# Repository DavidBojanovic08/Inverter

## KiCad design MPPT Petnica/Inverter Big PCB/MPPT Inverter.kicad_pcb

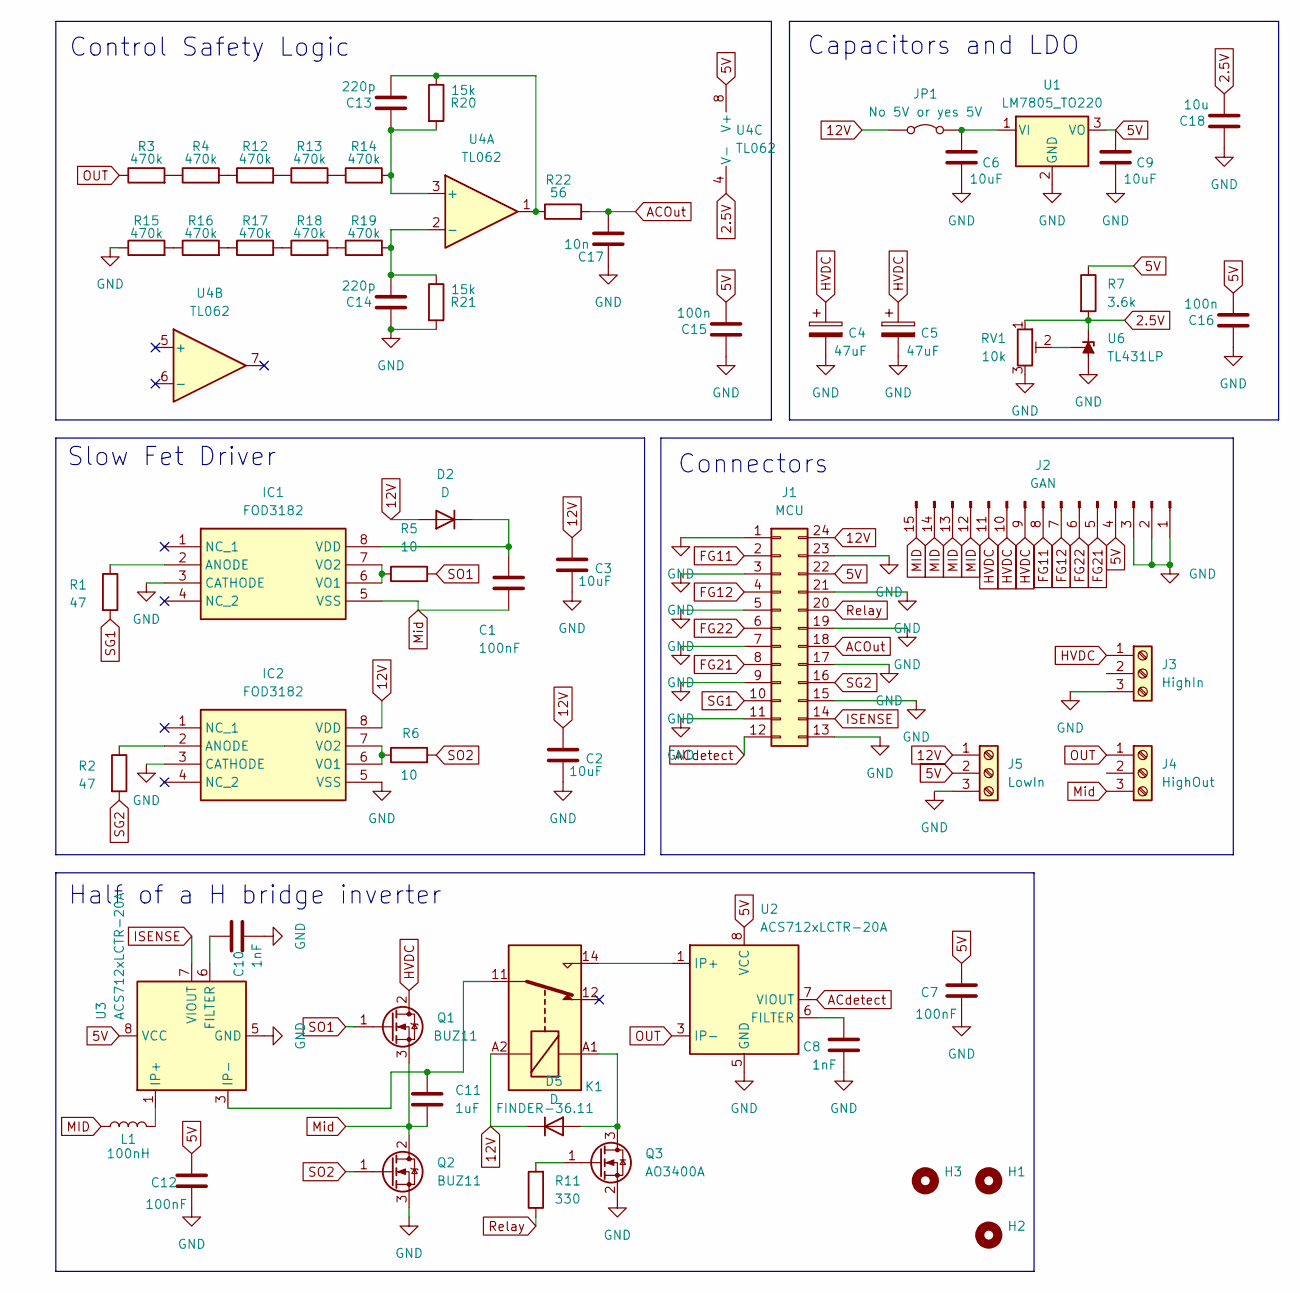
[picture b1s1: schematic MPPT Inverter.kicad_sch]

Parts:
C1, C7, C12: 100nF; C_0603_1608Metric
C2, C3, C6, C9: 10uF; C_0805_2012Metric
C4, C5: 47uF; CP_Radial_D16.0mm_P7.50mm
C8, C10: 1nF; C_0805_2012Metric
C11: 1uF; C_Rect_L29.0mm_W11.0mm_P27.50mm_MKT
C13, C14: 220p; C_0603_1608Metric
C15, C16: 100n; C_0603_1608Metric
C17: 10n; C_0603_1608Metric
C18: 10u; C_0805_2012Metric
D2: D; D_0603_1608Metric
D5: D; D_0805_2012Metric
H1, H2, H3: MountingHole; MountingHole_3.2mm_M3
IC1, IC2: FOD3182; Manufacturer_Part_Number FOD3182; Mouser Part Number 512-FOD3182
J1: MCU; IDC-Header_2x12_P2.54mm_Vertical
J2: GAN; PinHeader_1x15_P2.54mm_Vertical
J3: HighIn; TerminalBlock_MaiXu_MX126-5.0-03P_1x03_P5.00mm
J4: HighOut; TerminalBlock_MaiXu_MX126-5.0-03P_1x03_P5.00mm
J5: LowIn; TerminalBlock_MaiXu_MX126-5.0-03P_1x03_P5.00mm
JP1: No 5V or yes 5V; R_0402_1005Metric
K1: FINDER-36.11; Relay_SPDT_Finder_36.11
L1: 100nH; L_Toroid_Vertical_L31.8mm_W15.9mm_P13.50mm_Bourns_5700
Q1, Q2: BUZ11; TO-220-3_Vertical
Q3: AO3400A; SOT-23
R1, R2: 47; R_0603_1608Metric
R3, R4, R12, R13, R14, R15, R16, R17, R18, R19: 470k; R_0603_1608Metric
R5, R6: 10; R_0603_1608Metric
R7: 3.6k; R_0603_1608Metric
R11: 330; R_0603_1608Metric
R20, R21: 15k; R_0603_1608Metric
R22: 56; R_0603_1608Metric
RV1: 10k; Potentiometer_Bourns_3266W_Vertical
U1: LM7805_TO220; TO-220-3_Vertical
U2, U3: ACS712xLCTR-20A; SOIC-8_3.9x4.9mm_P1.27mm
U4: TL062; DIP-8_W7.62mm
U6: TL431LP; TO-92_Inline

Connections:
2.5V: C18.2, R7.2, RV1.1, U4.4 (V-), U6.3 (K)
5V: C7.1, C9.1, C12.1, C15.2, C16.2, J1.22, J2.4, J5.2, R7.1, U1.3 (VO), U2.8 (VCC), U3.8 (VCC), U4.8 (V+)
12V: C2.1, C3.1, D2.2 (A), D5.1 (K), IC2.8 (VDD), J1.24, J5.1, JP1.1 (A), K1.A2
ACOut: C17.2, J1.18, R22.2
ACdetect: J1.12, U2.7 (VIOUT)
FG11: J1.2, J2.8
FG12: J1.4, J2.7
FG21: J1.8, J2.5
FG22: J1.6, J2.6
GND: C2.2, C3.2, C4.2, C5.2, C6.2, C7.2, C8.2, C9.2, C10.2, C12.2, C14.1, C15.1, C16.1, C17.1, C18.1, IC1.3 (CATHODE), IC2.3 (CATHODE), IC2.5 (VSS), J1.1, J1.3, J1.5, J1.7, J1.9, J1.11, J1.13, J1.15, J1.17, J1.19, J1.21, J1.23, J2.1, J2.2, J2.3, J3.3, J5.3, Q2.3 (S), Q3.2 (S), R15.1, R21.2, RV1.3, U1.2 (GND), U2.5 (GND), U3.5 (GND), U6.2 (A)
HVDC: C4.1, C5.1, J2.9, J2.10, J2.11, J3.1, Q1.2 (D)
ISENSE: J1.14, U3.7 (VIOUT)
MID: J2.12, J2.13, J2.14, J2.15, L1.1
Mid: C1.2, C11.1, IC1.5 (VSS), J4.3, Q1.3 (S), Q2.2 (D)
unnamed: C11.2, K1.11, U3.3 (IP-), U3.4 (IP-)
unnamed: C13.2, R20.1, R22.1, U4.1
unnamed: C1.1, D2.1 (K), IC1.8 (VDD)
unnamed: D5.2 (A), K1.A1, Q3.3 (D)
unnamed: IC1.2 (ANODE), R1.1
unnamed: IC1.6 (VO1), IC1.7 (VO2), R5.1
unnamed: IC2.2 (ANODE), R2.1
unnamed: IC2.6 (VO1), IC2.7 (VO2), R6.1
unnamed: C6.1, JP1.2 (B), U1.1 (VI)
unnamed: K1.14, U2.1 (IP+), U2.2 (IP+)
unnamed: L1.2, U3.1 (IP+), U3.2 (IP+)
unnamed: Q3.1 (G), R11.2
unnamed: R3.2, R4.1
unnamed: R4.2, R12.1
unnamed: R12.2, R13.1
unnamed: R13.2, R14.1
unnamed: R15.2, R16.1
unnamed: R16.2, R17.1
unnamed: R17.2, R18.1
unnamed: R18.2, R19.1
unnamed: C8.1, U2.6 (FILTER)
unnamed: C10.1, U3.6 (FILTER)
unnamed: C13.1, R14.2, R20.2, U4.3 (+)
unnamed: C14.2, R19.2, R21.1, U4.2 (-)
unnamed: RV1.2, U6.1 (REF)
OUT: J4.1, R3.1, U2.3 (IP-), U2.4 (IP-)
Relay: J1.20, R11.1
SG1: J1.10, R1.2
SG2: J1.16, R2.2
SO1: Q1.1 (G), R5.2
SO2: Q2.1 (G), R6.2

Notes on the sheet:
Half of a H bridge inverter
Slow Fet Driver
Capacitors and LDO
Connectors
Control Safety Logic

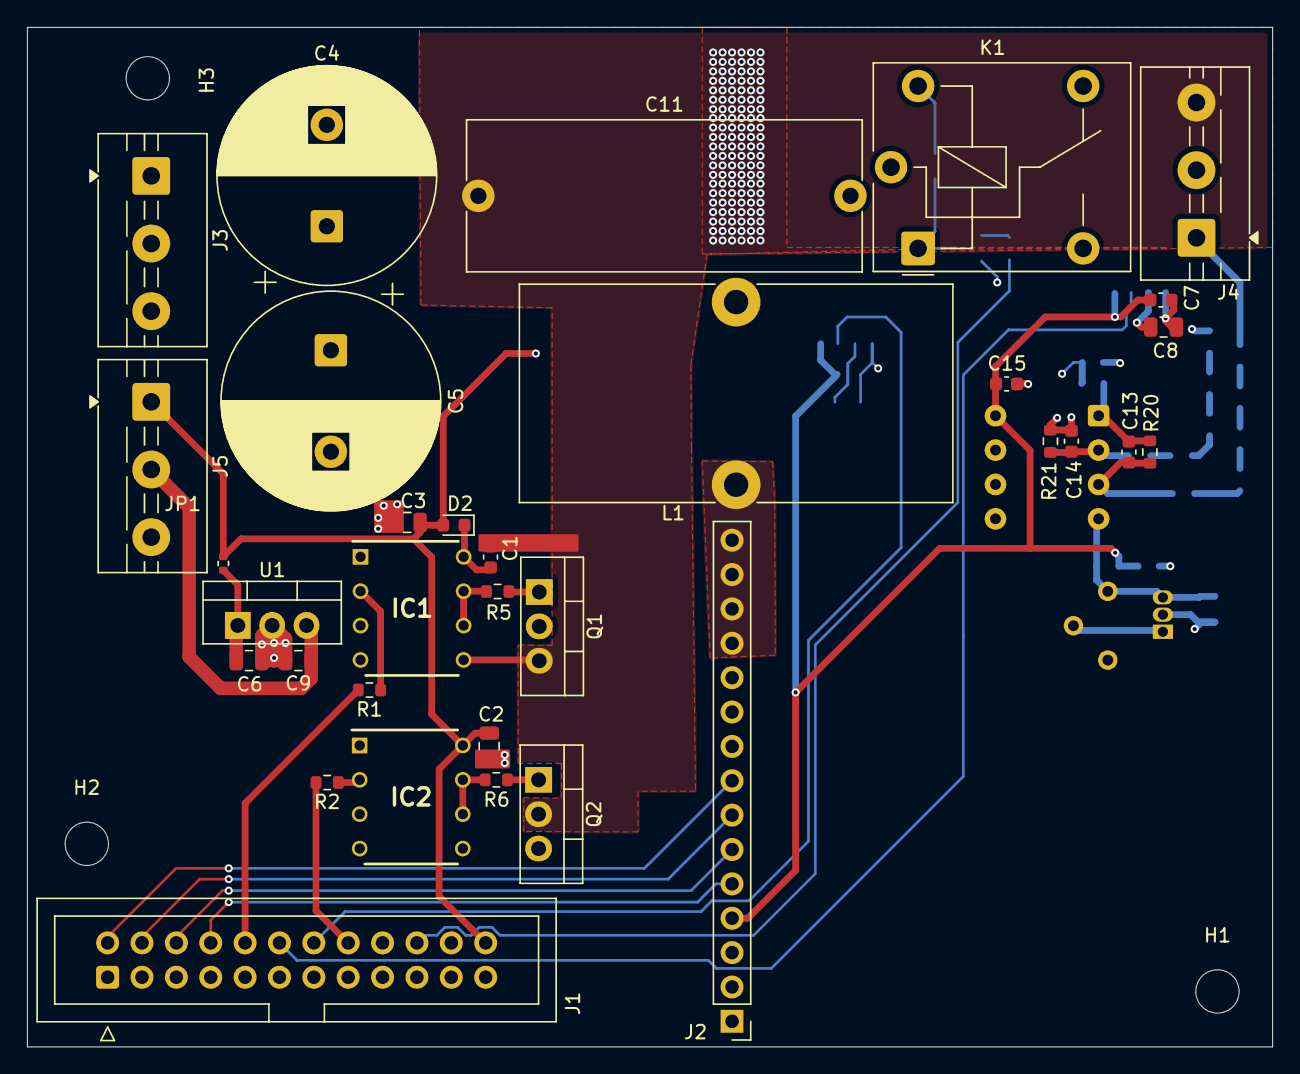
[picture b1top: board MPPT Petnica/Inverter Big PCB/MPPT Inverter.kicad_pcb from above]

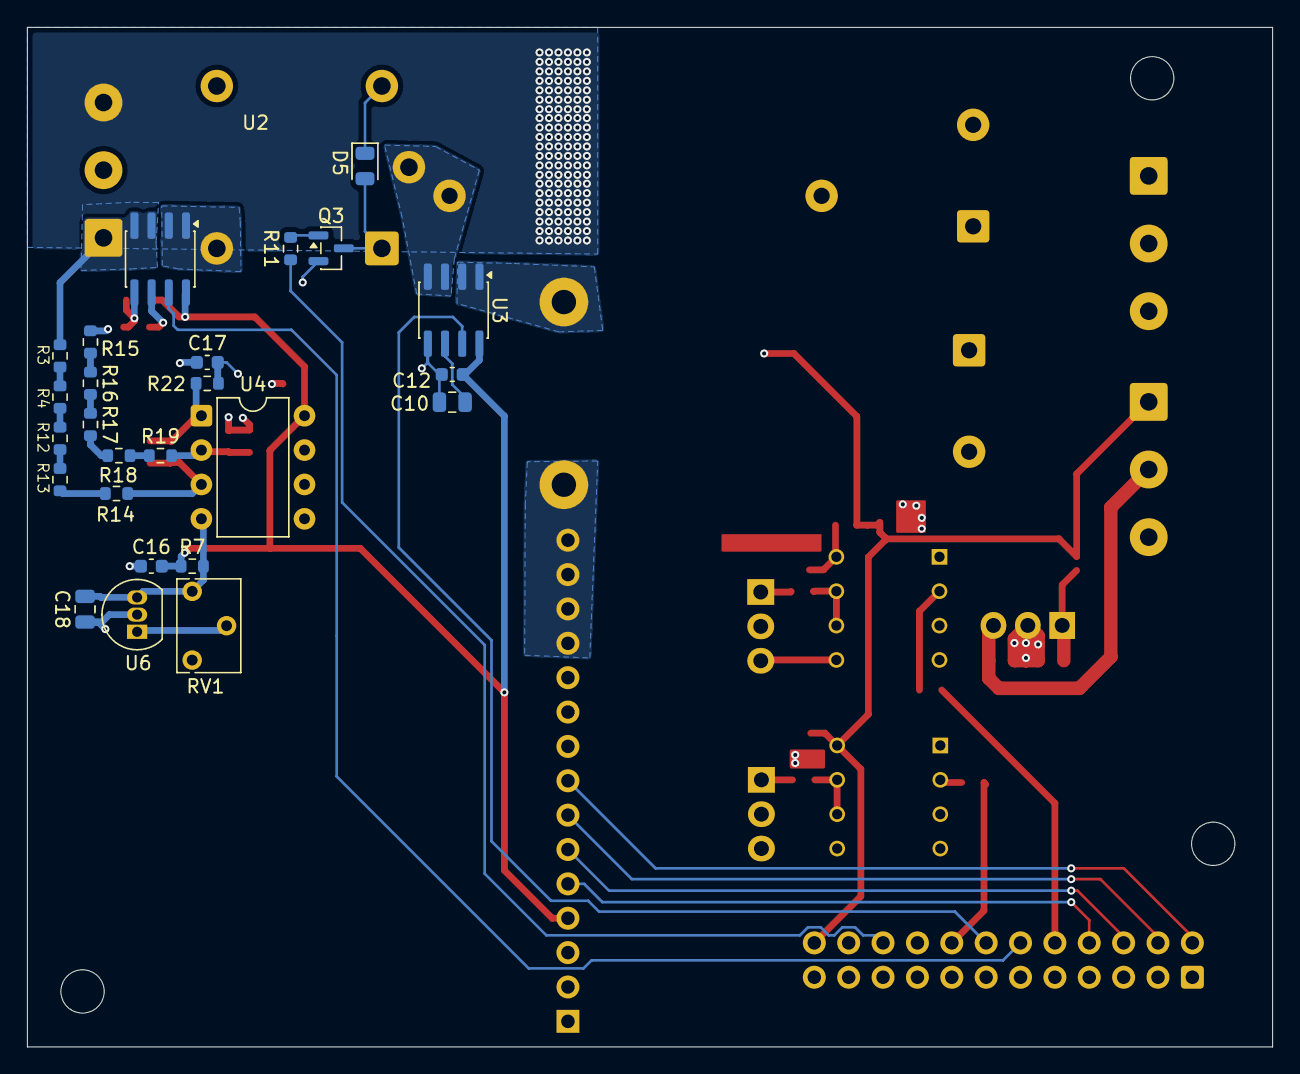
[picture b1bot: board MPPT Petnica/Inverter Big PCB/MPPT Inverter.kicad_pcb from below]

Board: 4 copper layers, 92.0 x 75.3 mm, 61 parts (25 on the bottom side), 45 nets.

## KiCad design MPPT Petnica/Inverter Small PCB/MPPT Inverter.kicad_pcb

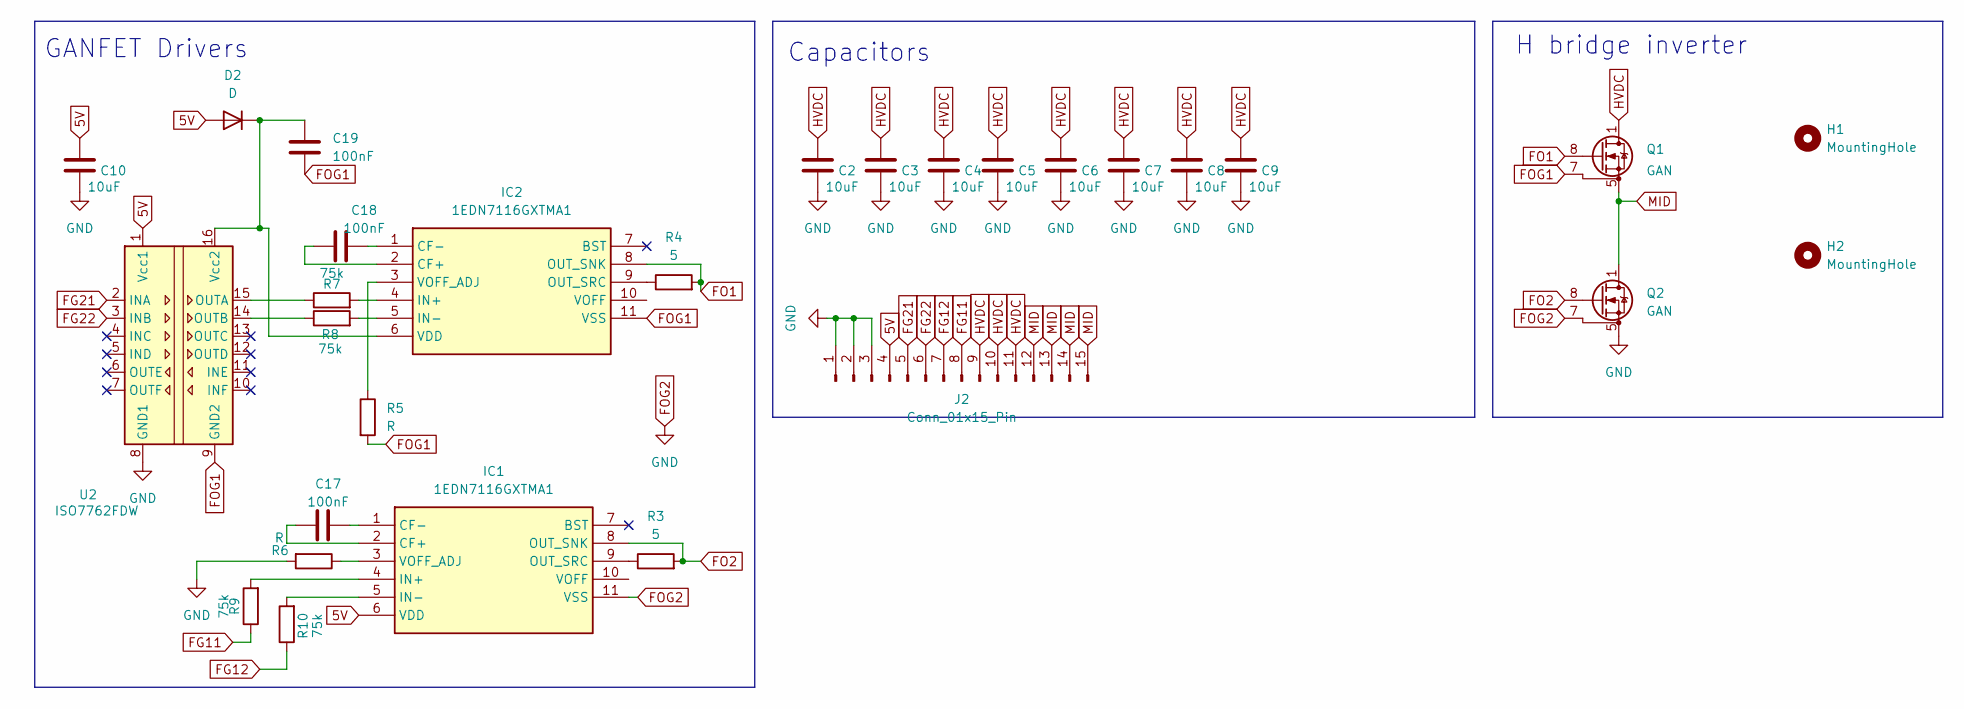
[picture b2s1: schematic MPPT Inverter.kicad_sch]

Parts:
C2, C3, C4, C5, C6, C7, C8, C9: 10uF; C_1206_3216Metric
C10: 10uF; C_0805_2012Metric
C17, C18, C19: 100nF; C_0805_2012Metric
D2: D; D_A-405_P7.62mm_Horizontal
H1, H2: MountingHole; MountingHole_2.2mm_M2
IC1, IC2: 1EDN7116GXTMA1; Manufacturer_Part_Number 1EDN7116GXTMA1; Mouser Part Number 726-1EDN7116GXTMA1
J2: Conn_01x15_Pin; PinHeader_1x15_P2.54mm_Horizontal
Q1, Q2: GAN; Panasonic_HSON-8_8x8mm_P2.00mm
R3, R4: 5; R_0805_2012Metric
R5, R6: R; R_0805_2012Metric
R7, R8, R9, R10: 75k; R_0805_2012Metric
U2: ISO7762FDW; SOIC-16W_7.5x10.3mm_P1.27mm

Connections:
5V: C10.1, D2.2 (A), IC1.6 (VDD), J2.4, U2.1 (Vcc1)
FG11: J2.8, R9.1
FG12: J2.7, R10.1
FG21: J2.5, U2.2 (INA)
FG22: J2.6, U2.3 (INB)
FO1: IC2.8 (OUT_SNK), Q1.8 (G), R4.2
FO2: IC1.8 (OUT_SNK), Q2.8 (G), R3.2
FOG1: C19.2, IC2.11 (VSS), Q1.7 (S1), R5.2, U2.9 (GND2)
FOG2: C2.2, C3.2, C4.2, C5.2, C6.2, C7.2, C8.2, C9.2, C10.2, IC1.11 (VSS), J2.1, J2.2, J2.3, Q2.5 (S2), Q2.6 (S2), Q2.7 (S1), Q2.9 (S2), R6.2, U2.8 (GND1)
HVDC: C2.1, C3.1, C4.1, C5.1, C6.1, C7.1, C8.1, C9.1, J2.9, J2.10, J2.11, Q1.1 (D), Q1.2 (D), Q1.3 (D), Q1.4 (D)
MID: J2.12, J2.13, J2.14, J2.15, Q1.5 (S2), Q1.6 (S2), Q1.9 (S2), Q2.1 (D), Q2.2 (D), Q2.3 (D), Q2.4 (D)
unnamed: C19.1, D2.1 (K), IC2.6 (VDD), U2.16 (Vcc2)
unnamed: C17.1, IC1.2 (CF+)
unnamed: C17.2, IC1.1 (CF-)
unnamed: IC1.4 (IN+), R9.2
unnamed: IC1.5 (IN-), R10.2
unnamed: IC1.9 (OUT_SRC), R3.1
unnamed: IC1.3 (VOFF_ADJ), R6.1
unnamed: C18.1, IC2.2 (CF+)
unnamed: C18.2, IC2.1 (CF-)
unnamed: IC2.4 (IN+), R7.2
unnamed: IC2.5 (IN-), R8.2
unnamed: IC2.9 (OUT_SRC), R4.1
unnamed: IC2.3 (VOFF_ADJ), R5.1
unnamed: R7.1, U2.15 (OUTA)
unnamed: R8.1, U2.14 (OUTB)

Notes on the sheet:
GANFET Drivers
H bridge inverter
Capacitors

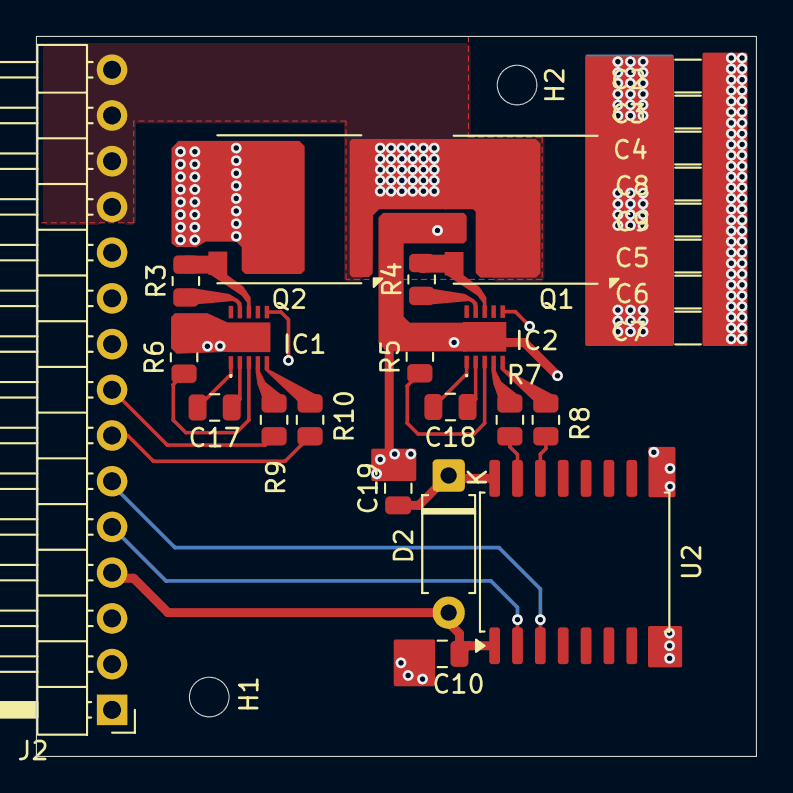
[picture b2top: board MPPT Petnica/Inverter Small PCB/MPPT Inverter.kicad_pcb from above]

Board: 4 copper layers, 40.0 x 40.0 mm, 29 parts (0 on the bottom side), 26 nets.
